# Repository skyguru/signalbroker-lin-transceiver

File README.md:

# LIN

How to setup the LIN transceiver

## Installation 

### Prerequisites

Download USB-drivers for the ESP-device, choose driver depending on OS here:
https://www.olimex.com/Products/IoT/ESP32/ESP32-POE/open-source-hardware 

For be available to upload this project to your device you need at least PlatformIO. 
You can either install it as a [CLI application](https://docs.platformio.org/en/latest/core/index.html#) but the prefferd way is to use their extension within an [IDE](https://docs.platformio.org/en/latest/integration/ide/pioide.html#).

I guess that the most popular is to use VS Code so I will use it in the example below.

#### VS Code

* [VS Code](https://code.visualstudio.com/)
* [PlatformIO Extension](https://marketplace.visualstudio.com/items?itemName=platformio.platformio-ide)

If you have installed the applications above, open this folder with VS Code.  

## Configuration

The thing you need to check/modify before upload is the rib id you assigning to the device. In order to do this, go to the main.cpp file placed in the src folder and change the variable. Remember the rib ID beacuse you need to setup the signalbroker server with this rib ID later. 

```cpp 
constexpr uint8_t rib_id = 1;
```

Now you are ready to upload this to your device!!

### Modify the interface.json on the server side

When you have uploaded the firmware to your ESP32-devices and assinged them with unique rib ID's. You need to configure the interfaces.json file on signalbroker-server side in the following way:

* namespace - Unique namespace name (Tip is to use Linbus and mode (master/slave) eg: LIN14-M)
* device_identifier - rib ID that you assigned to the device
* server/targetport - needs to be unique port for each device
* device_name - need as well be unique, to follow the example above for namespace: lin14m
* node_mode: master/slave depending on how the device is connected to the LIN bus
* ldf_file - paste the link to where you have the LDF file
* schedule_file - same as ldf_file
* schedule_table_name - which schduler you want to use when you are running the device as master
* schedule_autostart - master: true, slave: false
```json 
{
      "namespace": "LinSlave",
      "type": "lin",
      "config": {
        "device_identifier": 1,
        "server_port": 2014,
        "target_host": null,
        "target_port": 2013
      },
      "device_name": "lin",
      "node_mode": "slave",
      "ldf_file": "configuration/ldf_files/linone.ldf",
      "schedule_file": "configuration/ldf_files/linone.ldf",
      "schedule_table_name": "linoneSchedule",
      "schedule_autostart": false
}
```

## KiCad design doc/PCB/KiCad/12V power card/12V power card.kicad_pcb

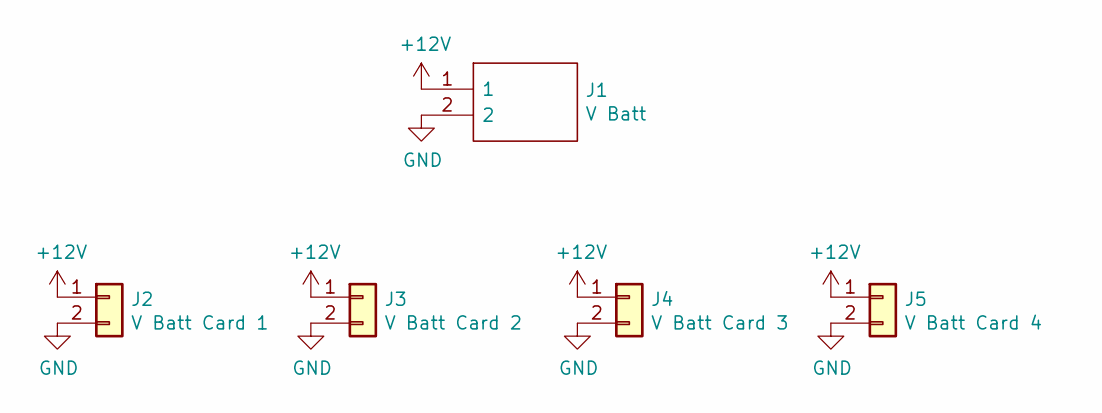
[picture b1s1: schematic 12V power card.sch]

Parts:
J1: V Batt; SHDR2W66P0X254_1X2_508X572X775P; Manufacturer_Part_Number 640456-2
J2: V Batt Card 1; PinSocket_1x02_P2.54mm_Vertical
J3: V Batt Card 2; PinSocket_1x02_P2.54mm_Vertical
J4: V Batt Card 3; PinSocket_1x02_P2.54mm_Vertical
J5: V Batt Card 4; PinSocket_1x02_P2.54mm_Vertical

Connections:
+12V: J1.1, J2.1, J3.1, J4.1, J5.1
GND: J1.2, J2.2, J3.2, J4.2, J5.2

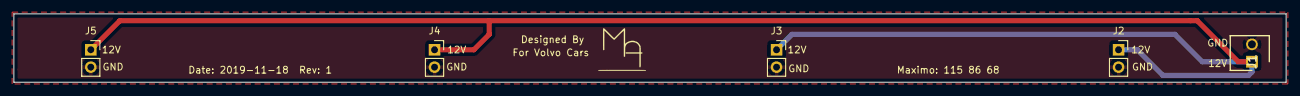
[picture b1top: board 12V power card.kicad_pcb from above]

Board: 2 copper layers, 186.0 x 10.0 mm, 5 parts (0 on the bottom side), 2 nets.

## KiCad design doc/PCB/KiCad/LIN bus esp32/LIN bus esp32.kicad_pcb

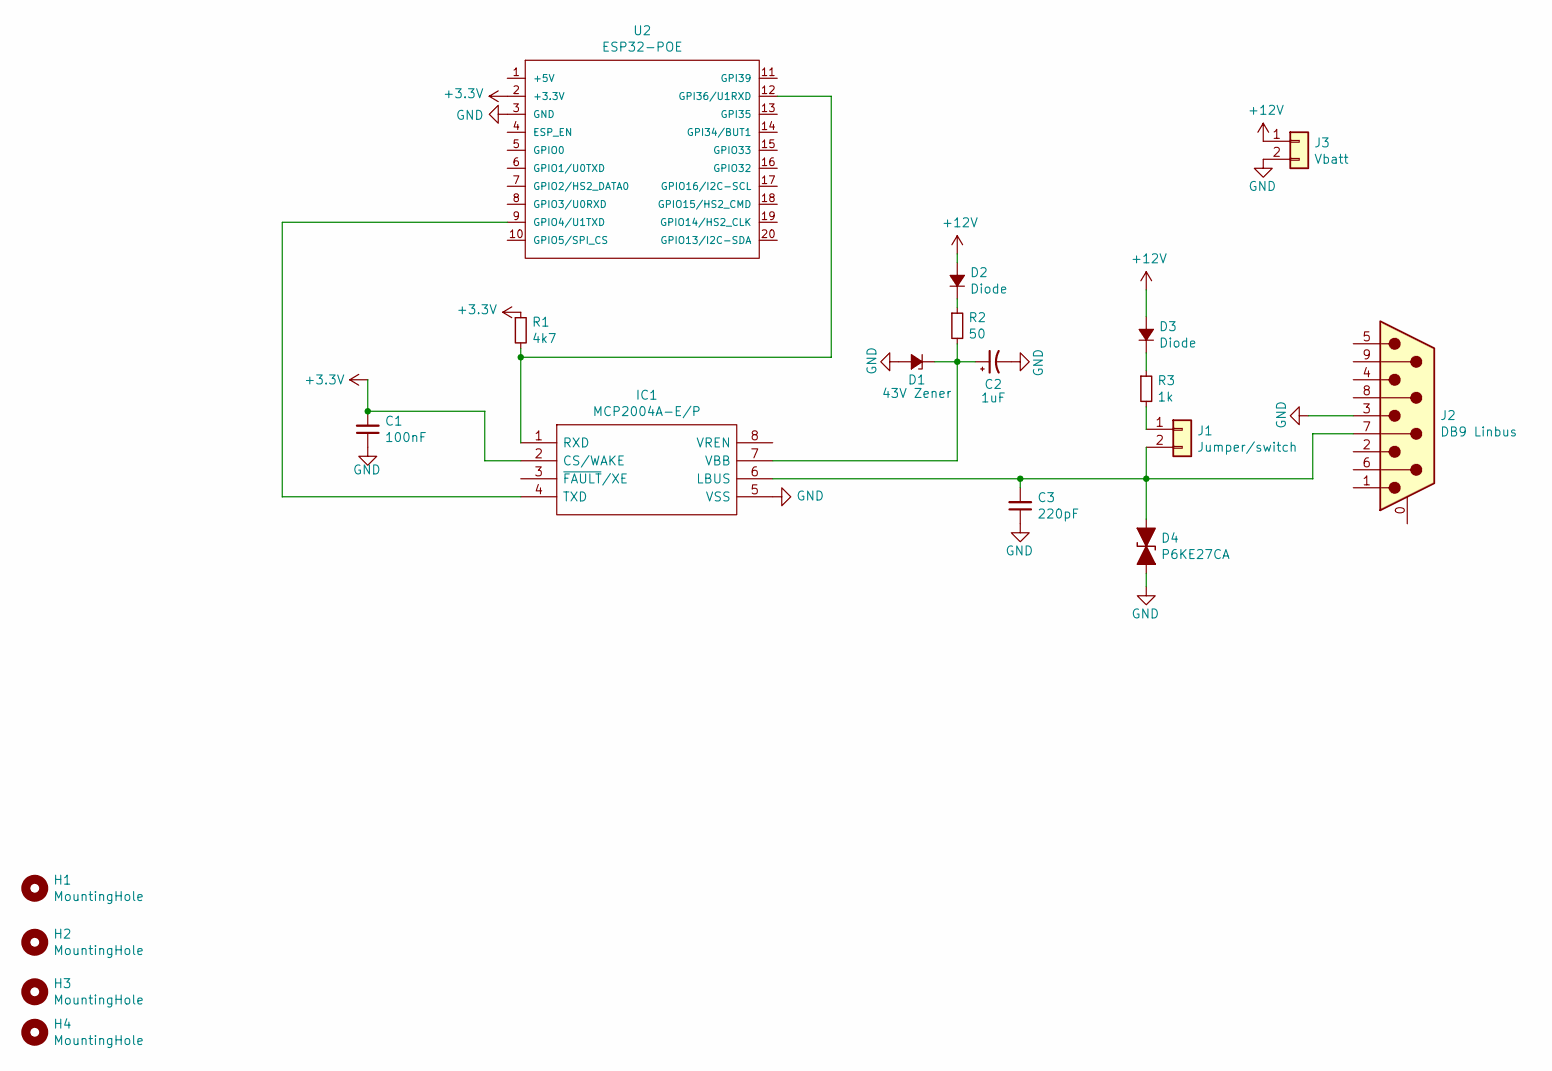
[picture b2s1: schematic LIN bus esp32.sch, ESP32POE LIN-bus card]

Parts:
C1: 100nF; C_Rect_L4.6mm_W2.0mm_P2.50mm_MKS02_FKP02
C2: 1uF; CP_Radial_Tantal_D7.0mm_P2.50mm
C3: 220pF; C_Rect_L4.6mm_W2.0mm_P2.50mm_MKS02_FKP02
D1: 43V Zener; D_DO-41_SOD81_P7.62mm_Horizontal
D2, D3: Diode; D_DO-15_P10.16mm_Horizontal
D4: P6KE27CA; D_DO-15_P12.70mm_Horizontal
H1, H2, H3, H4: MountingHole; MountingHole_3.2mm_M3
IC1: MCP2004A-E/P; DIP787W46P254L927H533Q8; Manufacturer_Part_Number MCP2004A-E/SN; Mouser Part Number 579-MCP2004AESN
J1: Jumper/switch; PinHeader_1x02_P2.54mm_Vertical
J2: DB9 Linbus; DSUB-9_Male_Horizontal_P2.77x2.84mm_EdgePinOffset9.90mm_Hou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
J3: Vbatt; PinHeader_1x02_P2.54mm_Horizontal
R1: 4k7; R_Axial_DIN0207_L6.3mm_D2.5mm_P10.16mm_Horizontal
R2: 50; R_Axial_DIN0207_L6.3mm_D2.5mm_P10.16mm_Horizontal
R3: 1k; R_Axial_DIN0207_L6.3mm_D2.5mm_P10.16mm_Horizontal
U2: ESP32-POE

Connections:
+3V3: C1.2, IC1.2 (CS/WAKE), R1.1, U2.2 (+3.3V)
+12V: D2.2 (A), D3.2 (A), J3.1
GND: C1.1, C2.2, C3.1, D1.2 (A), D4.2 (A2), IC1.5 (VSS), J2.3, J3.2, U2.3 (GND)
unnamed: C2.1, D1.1 (K), IC1.7 (VBB), R2.2
unnamed: C3.2, D4.1 (A1), IC1.6 (LBUS), J1.2, J2.7
unnamed: D2.1 (K), R2.1
unnamed: D3.1 (K), R3.1
unnamed: IC1.1 (RXD), R1.2, U2.12 (GPI36/U1RXD)
unnamed: IC1.4 (TXD), U2.9 (GPIO4/U1TXD)
unnamed: J1.1, R3.2

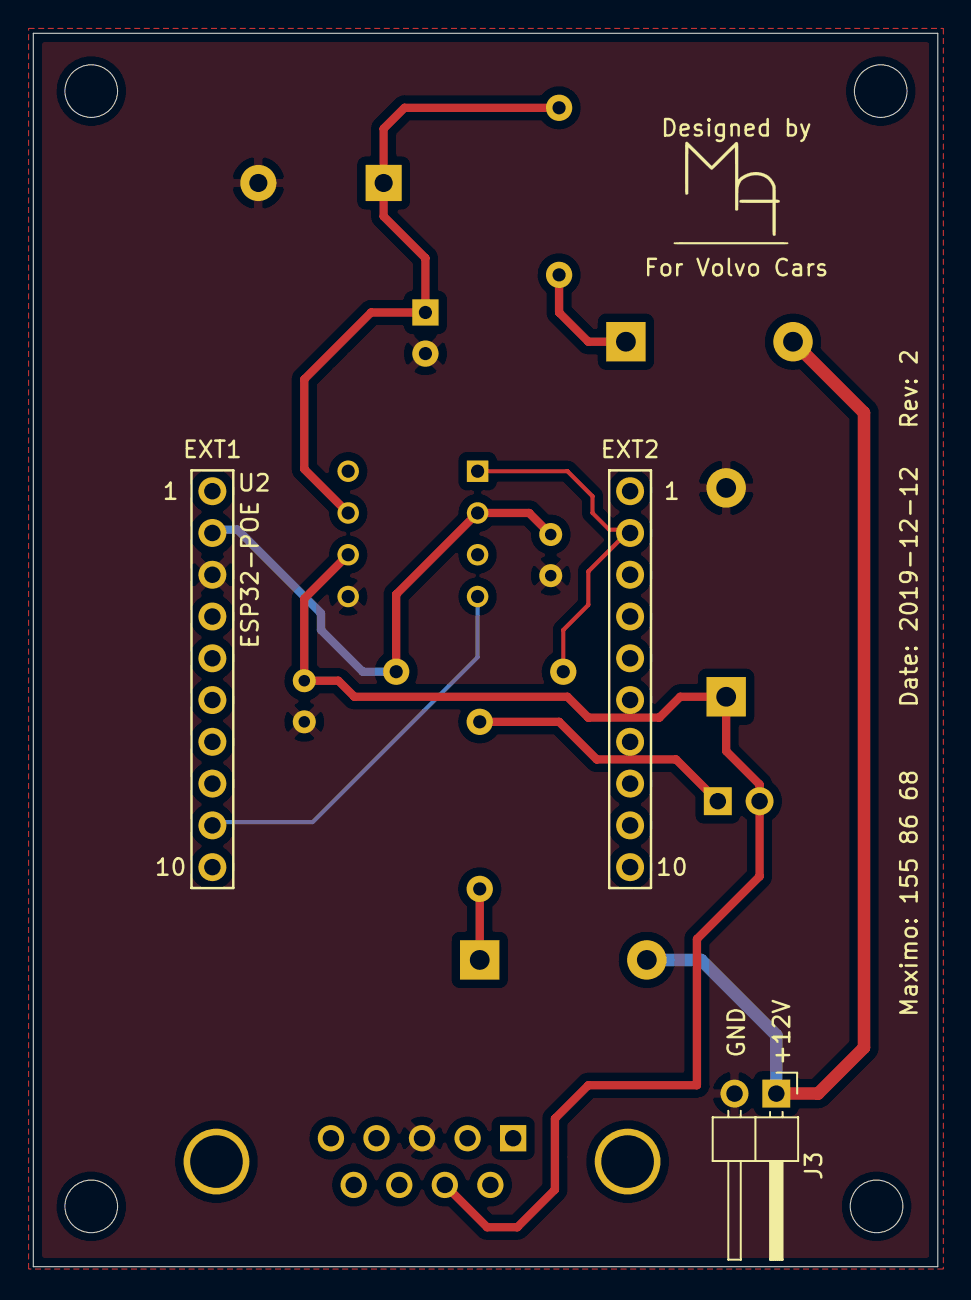
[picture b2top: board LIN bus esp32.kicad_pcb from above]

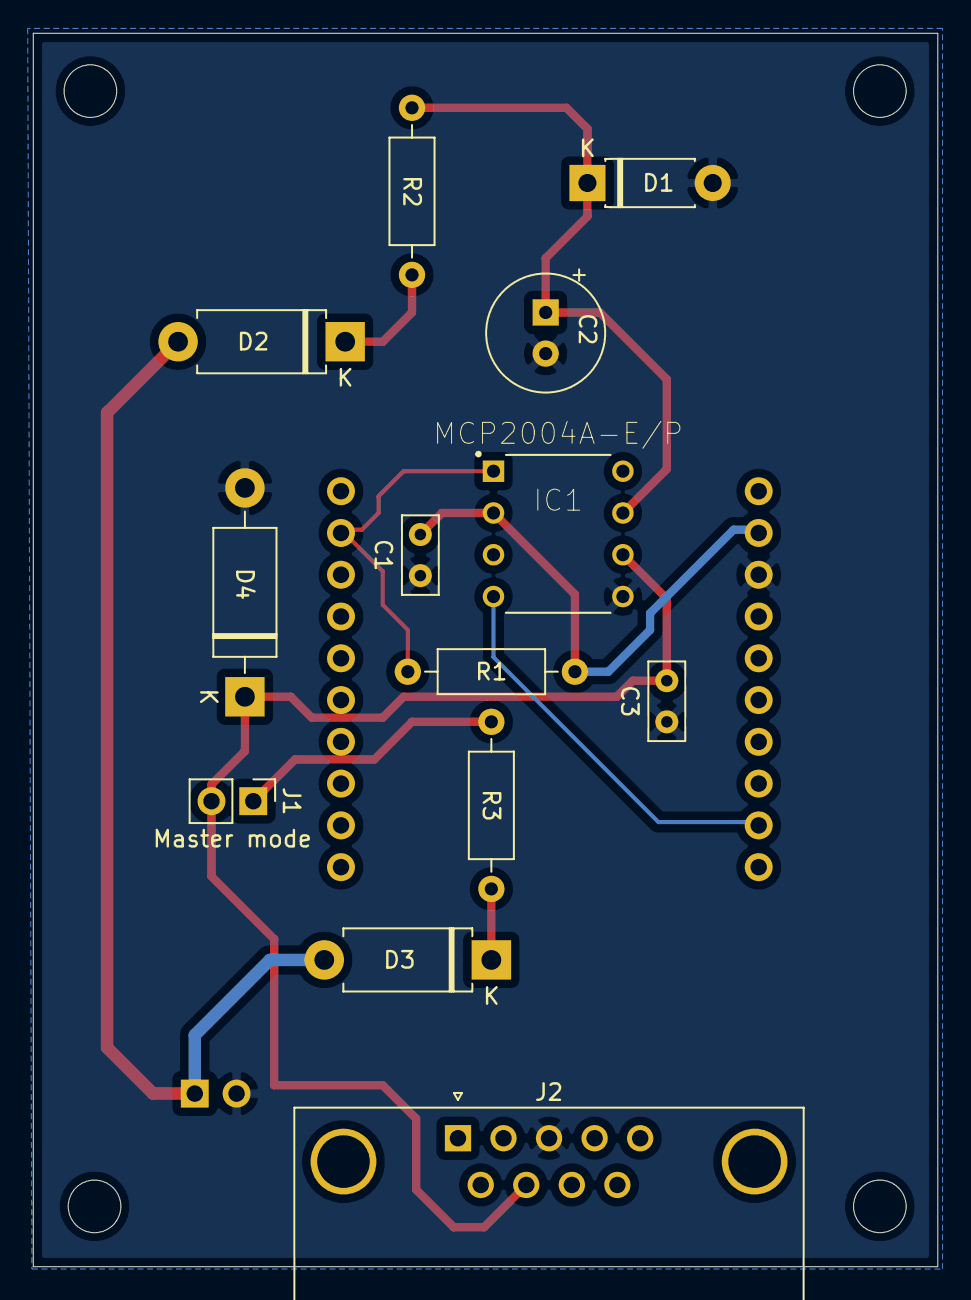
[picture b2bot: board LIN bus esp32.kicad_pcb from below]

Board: 2 copper layers, 55.0 x 75.0 mm, 19 parts (13 on the bottom side), 10 nets.

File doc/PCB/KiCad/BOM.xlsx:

Reference | Quantity | Value | Description | Manufacturer_Name | Manufacturer_Part_Number | Order from / available at | Link
Components for each LIN-bus transceiver module
C1 | 1 | 100nF | Capacitor |  |  | Volvo
C2 | 1 | 1uF | Capacitor Tantal |  |  | Volvo
C3 | 1 | 220pF | Capacitor |  |  | Volvo
D1 | 1 | BZX85/C43 | Zener diode 43V | Vishay |  | Elfa (170-06-802)
D3 D2 | 2 | 1N4007 | Diode |  |  | Volvo
D4 | 1 | P6KE27CA | VST Diode (ESD protection) | RND | RND P6KE27CA | Elfa (301-43-250)
IC1 | 1 | MCP2004A-E/P | LIN Transceivers Stand alone LIN Transceiver | Microchip | MCP2004A-E/P | Mouser (579-MCP2004AEP)
J1 | 1 | Jumper/switch | Pin header for selecting master node |  |  | Volvo
J2 | 1 | DB9 Linbus | DSUB 9pin Male PCB mount | Harting | 9651227801 | Farnell (2752008)
J3 | 1 | 2 | Pin header for Vbatt |  |  | Volvo
R1 | 1 | 4k7 | Resistor |  |  | Volvo
R2 | 1 | 50 | Resistor |  |  | Volvo
R3 | 1 | 1k | Resistor |  |  | Volvo
U2 | 1 | ESP32-POE | ESP32-POE | Olimex | ESP32-POE | Mouser (909-ESP32-POE)
U2 | 2 | 10 | Pinsocket |  |  | Volvo
IC1 | 1 | 1 | IC cradle |  |  | Volvo
Components for each box with 4 modules
 | 1 | RT3MP | mini/tiny XLR male chassi contact | Rean | RT3MP | Elfa (142-50-164)
 | 1 | RT3FC-B | mini/tiny XLR female contact | Rean | RT3FC-B | Elfa (142-50-161)

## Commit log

2019-04-05 Create LICENSE
2019-04-10 Added License header
2019-11-21 Test
2019-11-21 Change variable name
2019-11-21 Added comments & changing some debug info
2019-11-21 Added debug-serial-flag to this class
2019-11-21 Cleaned up the code, grouped variables that belongs together to enums
2019-11-21 Added esp32-linbus
2019-11-21 Added a common class, that have shared preferences
2019-11-21 Added submodule LIN
2019-11-21 Cleaning up
2019-11-21 Converting old C-style arrays to modern C++-arrays & added comments
2019-11-21 Moved out the functionsbodys to class instead of heaving them in the headerfile
2019-11-21 Added a function so we can access the last element of the array of Records
2019-11-21 Fixed typo in Filename
2019-11-21 Replaced Arduino linbus to ESP32 implementation
2019-11-21 Fixed a typo
2019-11-21 Added monitor_speed to be 115200 by deafult when we using this project
2019-11-21 Removed debug logger
2019-11-21 Changed class-member variables to start with _
2019-11-21 Added a Records-class that stores all Records we need
2019-11-21 Added comments, deleted that we created 20 empty objects in the constructor & now reserve 20 objects instead
2019-11-21 Added a gateway between lin-traffic and udp-communication
2019-11-21 Removed comment of old code
2019-12-04 Fill the array with zeros for more readability
2019-12-04 Removed unused UdpClient
2019-12-09 Added comments to see more clear what's happening
2019-12-13 Setted the right TX_PIN to the lin class
2019-12-13 Add comments for more readability, added variable for ribid, eth_connected & dhcp_enabled on top for easy change
2019-12-13 Added .gitignore file
2019-12-13 added gitignore for kicad files
2019-12-13 Added pcb design files adn BOM
2019-12-13 added pictures to be used in readme
2019-12-13 Updated gerbers
2019-12-13 Updated footprint for ESP32-POE
2019-12-13 Updated BOM
2019-12-14 Cleanup code from whitespaces unnecessary whitespaces
2019-12-14 Make the code more readable
2019-12-14 Changed the TRAFFIC_TIMEOUT to 13 to match timing in the esp32
2019-12-14 Formated code
2019-12-18 Removed that we are taking care of message comming from hostport
2019-12-19 Add .DS_STORE
2019-12-21 removed whitespace
2020-01-07 Updated the README with information about the PCB assembly
2020-01-07 Changed path to picture
2020-01-07 Changed path to picture (test)
2020-01-07 Small changes
2020-01-20 Increase the array so we are sure that we not read more data than the array can hold
2020-01-20 Check if the record is a nullpointer or not, if it is return from function
2020-01-20 Check if the bytes we recieved from serial match the record size, if it doesn't return
2020-01-20 If the bytes recieved from serial match the record size, increamnet counter RxOverLin
2020-01-20 Check if the calculated checksum match the recieved checksum from the serial
2020-01-20 Bulding up message that we are going to send to server, with id, size & data of LIN-message
2020-01-20 Send LIN buffer over serial
2020-01-20 Check if we have received any new data & the data is valid
2020-01-20 Handle incomming UPD-message that is valid
2020-01-20 Look if the id that is comming from UDP match any id from our records, if it does send the frame over serial otherwise return
2020-01-21 Changed url of remote submodule, I needed to make some changes to run it on ESP32
2020-01-21 Updated README with the description how to use this library with VSCode & PlatformIO
2020-08-26 updated license
2021-01-04 allow seperate config ports for up and downlink
2021-01-04 seperate ports operational
2021-01-06 stay compatible
2021-01-21 rotate server side
2021-02-23 implement swapbytes
2021-02-23 added dirs
2021-02-23 DS_STORE...
2021-02-28 added invalid record data
2021-02-28 added some documentation and debug print
2021-02-28 added documentation
2021-02-28 changed traffic timeout
2021-02-28 had an idea to use reference instead of pointers.. Not finished yet...
2021-02-28 changed format
2021-03-04 updated with two config ports (one up/one down)
2021-03-04 change time for LIN & changed to reference instead of pointer
2021-03-04 change to referenes instead of pointers
2021-03-04 idea stuffs
2021-03-05 cleanup
2021-03-05 fixed issue
2021-04-08 Deleted cpp file and have everything in header
2021-04-08 added comments
2021-04-08 Added task for sending heartbeat, so from now on the esp will not freeze any more
2021-04-08 changed client ID for ethernet
2021-04-08 deleted debug message
2021-04-08 changed version to 2.0
2021-04-08 deleted submodule
2021-04-13 bug fix
2021-04-13 removed upload port
2021-04-29 deleted invalid_id
2021-04-29 deleted task for sending heartbeat
2021-04-29 replace references with pointers
2021-04-29 added right monitor_speed
2021-05-17 updated LIN break
2021-05-17 updated formatting
2021-05-17 have two return statement instead of one
2021-05-17 added monitor filters
2021-05-31 support for NAD diagnostics, only relevant slave should act on request
